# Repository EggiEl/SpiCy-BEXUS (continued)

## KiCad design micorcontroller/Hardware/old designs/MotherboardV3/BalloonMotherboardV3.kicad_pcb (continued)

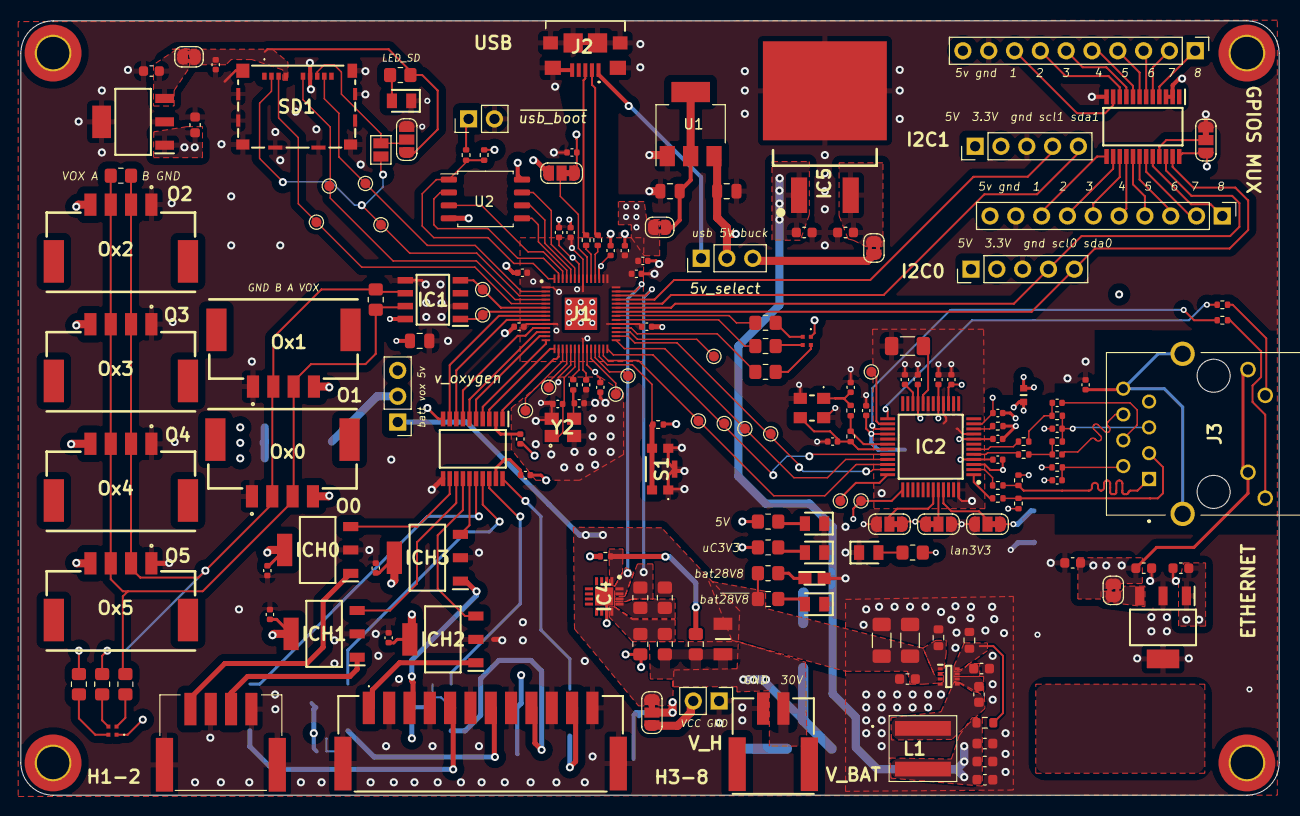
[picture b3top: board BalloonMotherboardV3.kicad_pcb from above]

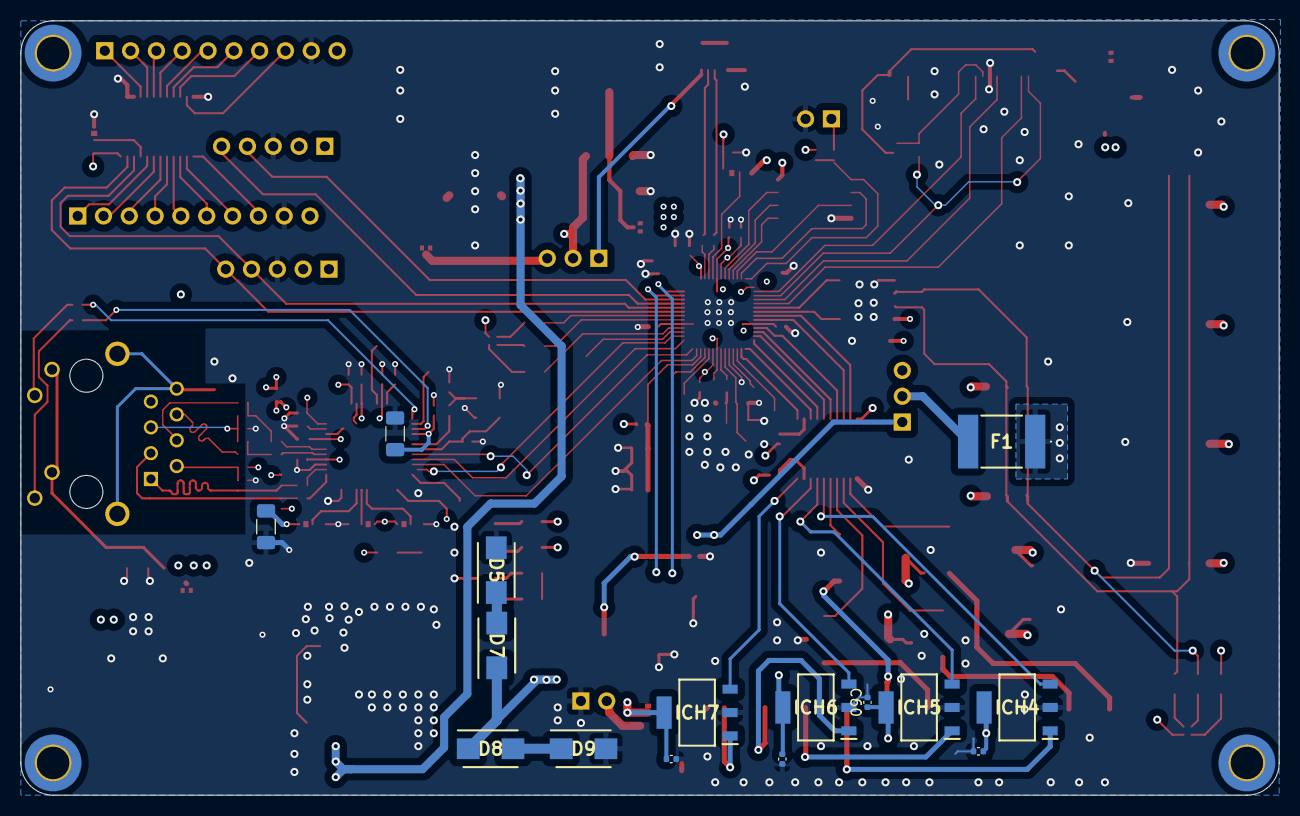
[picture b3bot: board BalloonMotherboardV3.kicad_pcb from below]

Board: 4 copper layers, 123.8 x 76.2 mm, 197 parts (15 on the bottom side), 156 nets.

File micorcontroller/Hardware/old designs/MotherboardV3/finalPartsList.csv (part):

Column1;Value;Cmp name;Footprint;Description;Vendor;DNP
C28, C30, C32, C33, C34, C35, C42;7;0.1uF;C;Capacitor_SMD:C_0402_1005Metric;Unpolarized capacitor;
C18, C19, C40, C41, C44, C46, C47, C48, C49, C50, C51;11;100n;C;Capacitor_SMD:C_0402_1005Metric;Unpolarized capacitor;
C54, C55, C56, C57, C58, C59, C60, C61;8;200nF;C;Capacitor_SMD:C_0402_1005Metric;Unpolarized capacitor;
C10;1;1nF/200V;C;Capacitor_SMD:C_0402_1005Metric;Unpolarized capacitor;
C1, C13;2;1u;C;Capacitor_SMD:C_0402_1005Metric;Unpolarized capacitor;
C12, C24;2;0.1u;C;Capacitor_SMD:C_0402_1005Metric;Unpolarized capacitor;
C15, C16;2;18p;C;Capacitor_SMD:C_0402_1005Metric;Unpolarized capacitor;
C29, C53;2;10nF;C;Capacitor_SMD:C_0402_1005Metric;Unpolarized capacitor;
C36, C37;2;15p;C;Capacitor_SMD:C_0402_1005Metric;Unpolarized capacitor;
C45, C52;2;6.8nF;C;Capacitor_SMD:C_0402_1005Metric;Unpolarized capacitor;
C9;1;22nF;C;Capacitor_SMD:C_0402_1005Metric;Unpolarized capacitor;
C11, C14, C17, C22;4;100nF;C;Capacitor_SMD:C_0603_1608Metric;Unpolarized capacitor;
C25;1;0.1uF;C;Capacitor_SMD:C_0603_1608Metric;Unpolarized capacitor;
C23;1;0.22uF;C;Capacitor_SMD:C_0603_1608Metric;Unpolarized capacitor;
C2, C7;2;0.47uF;C;Capacitor_SMD:C_0603_1608Metric;Unpolarized capacitor;
C4, C8;2;33uF;C;Capacitor_SMD:C_0603_1608Metric;Unpolarized capacitor;
C20, C21;2;22uF;C;Capacitor_SMD:C_0603_1608Metric;Unpolarized capacitor;
C3;1;33nF;C;Capacitor_SMD:C_0603_1608Metric;Unpolarized capacitor;
C26;1;1u;C;Capacitor_SMD:C_0805_2012Metric;Unpolarized capacitor;
C38, C39;2;10u;C;Capacitor_SMD:C_0805_2012Metric;Unpolarized capacitor;
C5, C6;2;10uF;C;Capacitor_SMD:C_1206_3216Metric_Pad1.33x1.80mm_HandSolder;Unpolarized capacitor;
C27, C43;2;10uF/16V;C;Capacitor_SMD:C_1206_3216Metric_Pad1.33x1.80mm_HandSolder;Unpolarized capacitor;
C31;1;4.7uF;C;Capacitor_SMD:C_1206_3216Metric_Pad1.33x1.80mm_HandSolder;Unpolarized capacitor;
;;;;;;
R29, R32, R33, R39, R40;5;0R;R_Small;Resistor_SMD:R_0402_1005Metric;Resistor, small symbol;
R16, R31, R37, R38;4;49R9 1%;R_Small;Resistor_SMD:R_0402_1005Metric;Resistor, small symbol;
R13;1;10R 1%;R_Small;Resistor_SMD:R_0402_1005Metric;Resistor, small symbol;
R67;1;10k but unessesary;R;Resistor_SMD:R_0402_1005Metric;Resistor;
R12;1;10k;R_Small;Resistor_SMD:R_0402_1005Metric;Resistor, small symbol;
R30;1;12.4k 1%;R_Small;Resistor_SMD:R_0402_1005Metric;Resistor, small symbol;
R27;1;1M;R_Small;Resistor_SMD:R_0402_1005Metric;Resistor, small symbol;
R1, R2;2;27;R;Resistor_SMD:R_0402_1005Metric;Resistor;
R14, R15;2;330;R_Small;Resistor_SMD:R_0402_1005Metric;Resistor, small symbol;
R66, R68;2;1k;R;Resistor_SMD:R_0402_1005Metric;Resistor;
R3;1;5k;R;Resistor_SMD:R_0402_1005Metric;Resistor;
R28;1;0;R_Small;Resistor_SMD:R_0603_1608Metric;Resistor, small symbol;
R5;1;10k;R_Small;Resistor_SMD:R_0603_1608Metric;Resistor, small symbol;
R6;1;90k;R_Small;Resistor_SMD:R_0603_1608Metric;Resistor, small symbol;
R4, R17, R20, R24, R34;5;680;R_Small;Resistor_SMD:R_0805_2012Metric_Pad1.20x1.40mm_HandSolder;Resistor, small symbol;
R11;1;100k;R_Small;Resistor_SMD:R_0805_2012Metric_Pad1.20x1.40mm_HandSolder;Resistor, small symbol;
R19;1;1500;R_Small;Resistor_SMD:R_0805_2012Metric_Pad1.20x1.40mm_HandSolder;Resistor, small symbol;
R7, R9;2;1k;R_Small;Resistor_SMD:R_0805_2012Metric_Pad1.20x1.40mm_HandSolder;Resistor, small symbol;
R8, R10;2;1M;R_Small;Resistor_SMD:R_0805_2012Metric_Pad1.20x1.40mm_HandSolder;Resistor, small symbol;
R18, R23;2;100;R_Small;Resistor_SMD:R_0805_2012Metric_Pad1.20x1.40mm_HandSolder;Resistor, small symbol;
R21, R22;2;12k;R_Small;Resistor_SMD:R_0805_2012Metric_Pad1.20x1.40mm_HandSolder;Resistor, small symbol;
R25, R35;2;270;R_Small;Resistor_SMD:R_0805_2012Metric_Pad1.20x1.40mm_HandSolder;Resistor, small symbol;
R26, R36;2;220;R_Small;Resistor_SMD:R_0805_2012Metric_Pad1.20x1.40mm_HandSolder;Resistor, small symbol;
;;;;;;
;;;;;;
Column1;Column2;Column3;Column4;Column5;Column6;Column7
R_shunt1;1;1mOhm;PA1206FRE7W0R001Z;SamacSys_Parts:RESC3216X90N;Current Sense Resistors - SMD 1mOhms 1/2W) 50PPM/C  1 % 1206 AEC-Q200;
Y2;1;ABM8G-12.000MHZ-4Y-T3;ABM8G-12.000MHZ-4Y-T3;ABM8G;Abracon 12MHz Crystal Unit +/-30ppm SMD 4-Pin 3.2 x 2.5 x 1mm;
J4;1;Conn_01x02;Conn_01x02;Connector_PinHeader_2.54mm:PinHeader_1x02_P2.54mm_Vertical;Generic connector, single row, 01x02, script generated (kicad-library-utils/schlib/autogen/connector/);
JHVA1;1;Conn_01x02;Conn_01x02;Connector_PinHeader_2.54mm:PinHeader_1x02_P2.54mm_Vertical;Generic connector, single row, 01x02, script generated (kicad-library-utils/schlib/autogen/connector/);
J5V2;1;Conn_01x03;Conn_01x03;Connector_PinHeader_2.54mm:PinHeader_1x03_P2.54mm_Vertical;Generic connector, single row, 01x03, script generated (kicad-library-utils/schlib/autogen/connector/);
JB_or_U1;1;Conn_01x03;Conn_01x03;Connector_PinHeader_2.54mm:PinHeader_1x03_P2.54mm_Vertical;Generic connector, single row, 01x03, script generated (kicad-library-utils/schlib/autogen/connector/);
scl0, scl1;2;Conn_01x05;Conn_01x05;Connector_PinHeader_2.54mm:PinHeader_1x05_P2.54mm_Vertical;Generic connector, single row, 01x05, script generated (kicad-library-utils/schlib/autogen/connector/);
J5, J6;2;Conn_01x10;Conn_01x10;Connector_PinHeader_2.54mm:PinHeader_1x10_P2.54mm_Vertical;Generic connector, single row, 01x10, script generated (kicad-library-utils/schlib/autogen/connector/);
H1, H2, H3, H4;4;MountingHole;MountingHole;MountingHole:MountingHole_3.2mm_M3_DIN965_Pad_TopBottom;Mounting Hole without connection;
U2;1;W25Q128JVS;W25Q128JVS;Package_SO:SOIC-8_5.23x5.23mm_P1.27mm;128Mb Serial Flash Memory, Standard/Dual/Quad SPI, SOIC-8;
U1;1;NCP1117-3.3_SOT223;NCP1117-3.3_SOT223;Package_TO_SOT_SMD:SOT-223-3_TabPin2;1A Low drop-out regulator, Fixed Output 3.3V, SOT-223;
J2;1;2174507-2;2174507-2;SamacSys_Parts:21745072;Conn Micro USB 2.0 Type B RCP 5 POS 0.65mm Solder RA SMD 5 Terminal 1 Port T/R;
S1;1;4,35E+11;4,35E+11;SamacSys_Parts:435441019830;Tactile Switches WS-TASV Tact Switch Washable 4.1x2.8x1.9 mm SMT;
V_BAT1;1;502352-0200;502352-0200;SamacSys_Parts:5023520200;Molex DURACLIK 502352, 2mm Pitch, 2 Way, 1 Row, Right Angle PCB Header, Surface Mount;
H1-2;1;502352-0400;502352-0400;SamacSys_Parts:5023520400;Molex DURACLIK 502352, 2mm Pitch, 4 Way, 1 Row, Right Angle PCB Header, Surface Mount;
H3-8;1;502352-1210;502352-1210;SamacSys_Parts:5023521210;DuraClik Wire-to-Board Header, Single Row, Right-Angle,  Circuits, Tin (Sn) Plating, Black;
Ox0, Ox1, Ox2, Ox3, Ox4, Ox5;6;560020-0420;560020-0420;SamacSys_Parts:560020-0420;Molex DURACLIK Series, Series Number 560020, 2mm Pitch 4 Way 1 Row Vertical PCB Header, 3A;
L1;1;74439346068;74439346068;SamacSys_Parts:74439346068;Wurth WE-XHMI Series Type 6060 Shielded Wire-wound SMD Inductor 6.8 uH +/-20% Wire-Wound 6.5A Idc;
FB1;1;BLM18SP102SZ1D;BLM18SP102SZ1D;SamacSys_Parts:BLM18SP221SN1B;Ferrite Beads 0603 1000ohm 25% INFO AEC-Q200;
IC5;1;L7805ACD2T-TR;L7805ACD2T-TR;SamacSys_Parts:D2PAK-STB35NF10T4;Voltage Regulator 5V 1A D2PAK STMicroelectronics L78xx L7805ACD2T-TR, Single Linear Voltage Regulator, 1.5A 5 V, +/-2%, 3-Pin D2PAK;
D5, D7, D9;3;D;D;SamacSys_Parts:DIOM5336X245N;Diode;
D8;1;RBR2LB60BTBR1;D;SamacSys_Parts:DIOM5336X245N;Diode;
Y1;1;ECS-250-6-33B2-CTP-TR;ECS-250-6-33B2-CTP-TR;SamacSys_Parts:ECS250633B2CTPTR;25 MHz +/-10ppm Crystal 6pF 40 Ohms 4-SMD, No Lead;
J3;1;J1B1211CCD;J1B1211CCD;SamacSys_Parts:J1B1211CCD;;
V_5V1;1;APTD2012LCGCK;APTD2012LCGCK_1;SamacSys_Parts:LEDC2012X120N;Standard LEDs - SMD 0805 Dome Lens LED Green- 570nm;
V_BATT1;1;APTD2012LCGCK;APTD2012LCGCK_1;SamacSys_Parts:LEDC2012X120N;Standard LEDs - SMD 0805 Dome Lens LED Green- 570nm;
V_LAN1;1;APTD2012LCGCK;APTD2012LCGCK_1;SamacSys_Parts:LEDC2012X120N;Standard LEDs - SMD 0805 Dome Lens LED Green- 570nm;
V_SD1;1;APTD2012LCGCK;APTD2012LCGCK_1;SamacSys_Parts:LEDC2012X120N;Standard LEDs - SMD 0805 Dome Lens LED Green- 570nm;
V_uC1;1;APTD2012LCGCK;APTD2012LCGCK_1;SamacSys_Parts:LEDC2012X120N;Standard LEDs - SMD 0805 Dome Lens LED Green- 570nm;
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
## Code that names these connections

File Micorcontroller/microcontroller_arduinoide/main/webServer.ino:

#define MISO_LAN 16
#define CS_LAN 17
#define SCK_LAN 18
#define MOSI_LAN 19
#define PORT 80

void testServer() {
  IPAddress ip(192, 168, 1, 177); 
  EthernetServer server(PORT); // (port 80 is default for HTTP):
  SPI.setRX(MISO_LAN);
  SPI.setTX(MOSI_LAN);
  SPI.setSCK(SCK_LAN);
  Ethernet.init(CS_LAN);

  while (!Serial) {}
  Serial.println("Ethernet WebServer Example");
  byte mac[] = { 0xDE, 0xAD, 0xBE, 0xEF, 0xFE, 0xED };
  Ethernet.begin(mac);  // Ethernet.begin(mac,ip);
  if (Ethernet.hardwareStatus() == EthernetNoHardware) {
    Serial.println("Ethernet shield was not found.  Sorry, can't run without hardware. :(");
    while (true) {
      delay(1);  // do nothing, no point running without Ethernet hardware
    }
  }
  if (Ethernet.linkStatus() == LinkOFF) {
    Serial.println("Ethernet cable is not connected.");
  }
  server.begin();
  Serial.print("server is at ");
  Serial.println(Ethernet.localIP());
  while (1) {  // listen for incoming clients
    EthernetClient client = server.available();
    if (client) {
      Serial.println("new client");
      // an HTTP request ends with a blank line
      bool currentLineIsBlank = true;
      while (client.connected()) {
        if (client.available()) {
          char c = client.read();
          Serial.write(c);
          // if you've gotten to the end of the line (received a newline
          // character) and the line is blank, the HTTP request has ended,
          // so you can send a reply
          if (c == '\n' && currentLineIsBlank) {
            // send a standard HTTP response header
            client.println("HTTP/1.1 200 OK");
            client.println("Content-Type: text/html");
            client.println("Connection: close");  // the connection will be closed after completion of the response
            client.println("Refresh: 5");         // refresh the page automatically every 5 sec
            client.println();
            client.println("<!DOCTYPE HTML>");
            client.println("<html>");
            // output the value of each analog input pin
            for (int analogChannel = 0; analogChannel < 6; analogChannel++) {
              int sensorReading = analogRead(analogChannel);
              client.print("analog input ");
              client.print(analogChannel);
              client.print(" is ");
              client.print(sensorReading);
              client.println("<br />");
            }
            client.println("</html>");
            break;
          }
          if (c == '\n') {
            // you're starting a new line
            currentLineIsBlank = true;
          } else if (c != '\r') {
            // you've gotten a character on the current line
            currentLineIsBlank = false;
          }
        }
      }
      // give the web browser time to receive the data
      delay(1);
      // close the connection:
      client.stop();
      Serial.println("client disconnected");
    }
  }
}

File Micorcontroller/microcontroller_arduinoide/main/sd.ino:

#define MISO_SD 0
#define MOSI_SD 3
#define CS_SD 1
#define SCK_SD 2

//if testing via breadboard make sure to just connect the SD Card and not the LAN
volatile uint8_t SD_init = 0;

unsigned long int max_freq_sd() {
  debug("-{sd_freq_calib-");
  unsigned long int freq = 1000000;  //first frequency to check
  SPI.setRX(MISO_SD);
  SPI.setTX(MOSI_SD);
  SPI.setSCK(SCK_SD);

  if (SD.begin(CS_SD)) {  // test if SD card is working at all
    SD.end();             // Serial.println("SD card working.");
  } else {
    debug("failed_default_f}-");
    return 0;
  }

  //tries different speeds

  for (uint8_t overflow = 0; overflow < 50; overflow++) {  //tries 1M steps
    if (SD.begin(CS_SD, freq)) {
      SD.end();
      freq = freq + 1000000;
    } else {
      freq = freq - 1000000;
      break;
    }
  }

  for (uint8_t overflow = 0; overflow < 50; overflow++) {  //tries 100k steps
    if (SD.begin(CS_SD, freq)) {
      SD.end();
      freq = freq + 100000;
    } else {
      freq = freq - 100000;
      break;
    }
  }

  for (uint8_t overflow = 0; overflow < 50; overflow++) {  //tries 10k steps
    if (SD.begin(CS_SD, freq)) {
      SD.end();
      freq = freq + 10000;
    } else {
      freq = freq - 10000;
      break;
    }
  }

  SD.end();
  debug("-freq:");
  debug(freq);
  debug("-sucess}-");
  return freq;
}

// initializes the SD card with the corresponding SPI pins
void init_SD() {
  if (SD_init) {debug("-SD_init=true-");}
  debug("-{SD_init-");
  SPI.setRX(MISO_SD);
  SPI.setTX(MOSI_SD);
  SPI.setSCK(SCK_SD);
  if (!SD.begin(CS_SD, max_freq_sd() * 0.8)) {
    debugln("failed}-");
    SD_init = 0;
  } else {
    debugln("sucess}-");
    SD_init = 1;
  }
}

int sd_numpackets(const char filepath[]) {
  debug("-{SD_sd_sizesavedpackets-file:");
  debug(filepath);
  if (!SD_init) { init_SD(); }
  File myFile = SD.open(filepath, FILE_WRITE);
  if (myFile) {
    debug("numberpackets:");
    debug(myFile.position() / sizeof(struct packet));
    debugln("-sucess}-");
    return myFile.position() / sizeof(struct packet);
  } else {
    debugln("-error:SDopening-failed}-");
    return -1;
  }
}


// writes a struct to sd card
bool writestruct(struct packet s_out, const char filepath[]) {
  debug("-{SD_writestru.id:");
  debug(s_out.id);
  debug("-file:");
  debug(filepath);
  if (!SD_init) { init_SD(); }
  uint8_t* buffer = (uint8_t*)malloc(sizeof(struct packet));
  memcpy(buffer, &s_out, sizeof(struct packet));  //converts struct in a char array
  File myFile = SD.open(filepath, FILE_WRITE);
  if (myFile) {  // if the file opened okay, write to it:
    myFile.write(buffer, sizeof(struct packet));
    free(buffer);
    myFile.close();
    debugln("-sucess}-");
    return 1;
  } else {
    debugln("-error:opening-failed}-");
    return 0;
  }
}

// reads a struct from sd card @position = position of struct packet
bool readstruct(struct packet* data, const char filepath[], unsigned long position) {
  debug("-{SD_readstru-file:");
  debug(filepath);
  if (!SD_init) { init_SD(); }
  File myFile = SD.open(filepath, FILE_READ);
  if (myFile) {
    if (!myFile.available()) {  //can be openend but is empty
      debug("-SDopeningsuccess-error:size(file)=");
      debug(myFile.available());
      debugln("}-");
      return 0;
    }
    uint8_t* buffer = (uint8_t*)malloc(sizeof(struct packet));
    if (!myFile.seek(position * sizeof(struct packet))) {
      debugln("-error:SDpositioning failed}-");
      return 0;
    }
    myFile.read(buffer, sizeof(struct packet));
    memcpy(data, buffer, sizeof(struct packet));
    free(buffer);
    myFile.close();
    debugln("-sucess}-");
    return 1;
  } else {
    debugln("-error:SDopening-failed}-");
    return 0;
  }
}

bool writetofile() {
  if (!SD_init) { init_SD(); }
  File myFile = SD.open("test.txt", FILE_WRITE);
  if (myFile) {  // if the file opened okay, write to it:
    Serial.print("Writing to test.txt...");
    myFile.println("testing 1, 2, 3.");
    myFile.close();
    Serial.println("done.");
  } else {
    Serial.println("error opening test.txt");  // if the file didn't open, print an error:
  }
  return 0;
}

bool printfile() {
  if (!SD_init) { init_SD(); }
  File myFile = SD.open("test.txt");
  if (myFile) {
    Serial.println("test.txt:");
    while (myFile.available()) {  // read from the file until there's nothing else in it:
      Serial.write(myFile.read());
    }
    myFile.close();
  } else {
    Serial.println("error opening test.txt");  // if the file didn't open, print an error:
  }
  return 1;
}

void testSD() {
  while (!Serial) {}

  init_SD();
  char filepath[] = "test.txt";
  SD.remove(filepath);

  struct packet data = packet_create();
  writestruct(data, filepath);
  data.info[0] = 100;
  debugln(data.timestampPacket);

  struct packet data1 = packet_create();
  writestruct(data1, filepath);
  data1.info[0] = 101;
  debugln(data1.timestampPacket);

  debugln(sd_numpackets(filepath));

  struct packet i;
  readstruct(&i, filepath, 0);
  Serial.println(i.info[0], DEC);
  Serial.println(i.timestampPacket);

  readstruct(&i, filepath, 1);
  Serial.println(i.info[0], DEC);
  Serial.println(i.timestampPacket);
}

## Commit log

2024-02-27 Backend Projekt aufgesetzt
2024-02-27 added uC Code and Groundstation python link
2024-02-27 some cleanup
2024-02-28 added dummy csv in gitignore
2024-02-28 Added Event listener for csv. Added Database Python Class for MongoDB. Added functions for database insertion
2024-02-29 static ip update
2024-02-29 gotta puh this to so the thing is empty
2024-02-29 cleanup data
2024-02-29 serverv3
2024-02-29 Backend get Request struct for stored Data
2024-03-01 Saved backend for localhost only requests. Same needed with frontend later
2024-03-01 Frontend Struktur aufgesetzt
2024-03-01 database access
2024-03-02 some refactoring of th uC
2024-03-02 updates Serverv3
2024-03-02 Mongo integrated
2024-03-02 ignores now rawdata
2024-03-02 ignores now rawdata v2
2024-03-02 Added feature to MongoDB, more than one sensor collection now possible with the same class-method implemented it in Serverv3 but not active
2024-03-04 Added Model Funktion for Sensor and getAllData Function. Tested Database connection read and write
2024-03-13 adding automated heating tests
2024-03-14 Added first Actitvity Diagramm for API function GETALL
2024-03-17 added some descriptions of my mess called embedded code
2024-03-17 added atlas sensor compability
2024-03-18 broke TCP server <skull emogi>
2024-03-20 fixed ips
2024-03-25 New function which searches the latest new entries in database
2024-03-25 some shifting around
2024-03-25 added shrek
2024-03-25 better circuit pictures
2024-03-25 changed scematic picture
2024-03-25 moving stuff around
2024-03-25 sd rework
2024-03-25 Basic Code
2024-03-26 get_latest_data function implemented and tested
2024-03-26 Python abh. hinzugefügt für Projekt clonen
2024-03-26 Frontend Plot UML
2024-03-26 Backend UML added for getNewerEntries()
2024-03-26 some moving around
2024-03-27 Class Diagramm, actitvity Diagramm frontend
2024-04-03 added NTC calculation
2024-04-03 get_all_data() function for frontend implemented and tested
2024-04-03 some spicy planuml updates
2024-04-03 notes
2024-04-03 update on main wiki page
2024-04-03 changed UML
2024-04-03 Frontend Code experiments
2024-04-10 Overall Software architecture uml
2024-04-11 propper Serial Comand System added
2024-04-14 added a serial command field for easy debugging
2024-04-19 Switch to header BASED C file system {headache incomming}
2024-04-20 rought prototype SingleFileUsb added
2024-04-20 update config
2024-04-21 added timebase watching function for the frontend plot
2024-04-21 switched to plattform pio <3
2024-04-26 startup message
2024-04-26 adding colours
2024-04-27 added some colouring and strength to the tcp client
2024-04-30 added a console and corors to the server
2024-04-30 restructuring Server4 code to improve readability
2024-04-30 reworked Server controllloop
2024-05-09 Improved TCP Server
2024-05-10 Making Server prettyer again
2024-05-12 added uplink
2024-05-17 Plot Component main comp finished
2024-05-17 deleted oldplot component
2024-05-17 fixed type error
2024-05-17 integrated and tested second plot component
2024-05-23 changed debug to level based debug and started writing driver for FD-OEM Module
2024-06-14 added some basic sliders
2024-06-23 Fixed some of the types
2024-06-23 Bump braces from 3.0.2 to 3.0.3 in /backend
    Bumps [braces](https://github.com/micromatch/braces) from 3.0.2 to 3.0.3.
    - [Changelog](https://github.com/micromatch/braces/blob/master/CHANGELOG.md)
    - [Commits](https://github.com/micromatch/braces/compare/3.0.2...3.0.3)
    ---
    updated-dependencies:
    - dependency-name: braces
2024-06-28 trying to fix things
2024-06-28 misted the files out a bit
2024-06-28 dded Server 7
2024-06-28 clean some things up
2024-06-28 fixed it
2024-06-28 added unstageds files
2024-06-28 modified old revison to get t up and running again
2024-06-28 changed array handeling from stack to heap
2024-06-28 made state mashine work
2024-07-02 cleanup
2024-07-02 trying to fix2
2024-07-02 renamend mirocontroller in motherboard
2024-07-02 deleted unnesseary stuff
2024-07-02 disables log files
2024-07-03 changed opamp
2024-07-03 backup files
2024-07-03 refined thermal controller
2024-07-04 thermal calcuation
2024-07-05 reworked command upload
2024-07-07 working on thermal
2024-07-07 worked on thermals
2024-07-08 temperature update
2024-07-09 did something
2024-07-09 ccpeck fixes
2024-07-12 got oxygensensor switching and measuring reliably
2024-07-13 worked on fd-oem modules
2024-07-13 made inits volitile and fixed mutithreading
2024-07-22 Fixed dependencies
2024-07-22 Fixed another dependency error
2024-07-22 Oxygen Struct for database
2024-07-22 struct for ox-measurement structure is now in the database python class
2024-07-24 added inrush current limiter
2024-07-25 GetNewer entries for Oxdata is now worling
2024-07-25 Frontend Plot for Ox Sensor working, needs to update on new Data though
2024-07-25 Added all oxgen Sensors, UI and a little bit of spicy-style *
2024-07-26 fixing pin issue with USART
2024-07-26 updated light sensors
2024-07-27 Styling for UX
2024-07-28 tweaked sd managment
2024-07-28 adjusted some pi controller values
2024-07-29 Added Time Measurement Feature
2024-07-29 worked on thepi controller
2024-08-06 added optional pressure sensor
2024-08-08 Some refactoring on the components
2024-08-12 refinig server
2024-08-14 updated thermals and integrated into server
2024-08-14 added error corruption detection
2024-08-14 Added conversion from bytes stream to dictionary
2024-08-14 linear aporx of last plot
2024-08-14 added documentation
2024-08-17 added more documentation
2024-08-17 deleted bloat
2024-08-17 changed pi controller form static values to struct based to enable more than one sensor at once
2024-08-17 reworked error system
2024-08-17 uplaod saferty copies
2024-08-17 added setup for struct based pi controller
2024-08-18 added testing result
2024-08-18 changed folder
2024-08-18 added files
2024-08-19 splitted header to header and config
2024-08-19 reworked printf statements
2024-08-19 replace pid with pi_controller
2024-08-19 deleted pid.cpp as replaced with pi_controller
2024-08-20 added function to add dummy data
2024-08-20 random python stuff
2024-08-21 New slider, better perfomrance and style
2024-08-21 added ota update
2024-08-22 changed command structure to allow any bytes to be send
2024-08-22 minor improvements on ota
2024-08-23 checked memory safety
2024-08-24 got OTA updateds running. Also tcp_sendf is running but still a bit buggy
2024-08-26 added light sensors
2024-08-27 fixed ota issues
2024-09-01 updates pre TVAC
2024-09-02 Temperatur from struct is now safed in mongoDB
2024-09-02 Backend service for Temperature plot
2024-09-02 Added Temperatur plot
2024-09-09 connected the oxsensors in the mongoDB class
2024-09-14 Added lower, upperlimit and plot limitation input fields
2024-09-14 Fixed typo
2024-09-23 Added a little bit of final styling
2024-09-24 changed to add light sensors
2024-09-25 added documentary
2024-09-25 changed print error line
2024-09-28 safety commit
2024-09-28 added heater PWM to Temperature plots
2024-09-29 Added Backend for other Data
2024-09-29 Safety commit of the otherplots
2024-09-29 Timestamp ox fixed
2024-09-29 removed all the rawdata.bin files
2024-09-29 Deleted debug msg
2024-09-30 IP ADRESS change
2024-09-30 ip change
2024-09-30 compiled server
2024-09-30 Styling version with two plots side by side
2024-10-01 Interference Test Data
2024-10-03 styling safe i forgotted to commit
2024-10-03 Added log from the launch attempt in as txt, added db as bson format in the same folder
2024-10-04 Night test for data
2024-10-04 Launch Data!!!
2024-10-05 biolabtest ende
2024-10-19 added some pictures
2024-10-19 removed bloat
2024-10-19 more pictures
2024-10-19 cropped
2024-12-13 added video of the console
2025-11-19 started on paper
2025-12-02 added gitignore
